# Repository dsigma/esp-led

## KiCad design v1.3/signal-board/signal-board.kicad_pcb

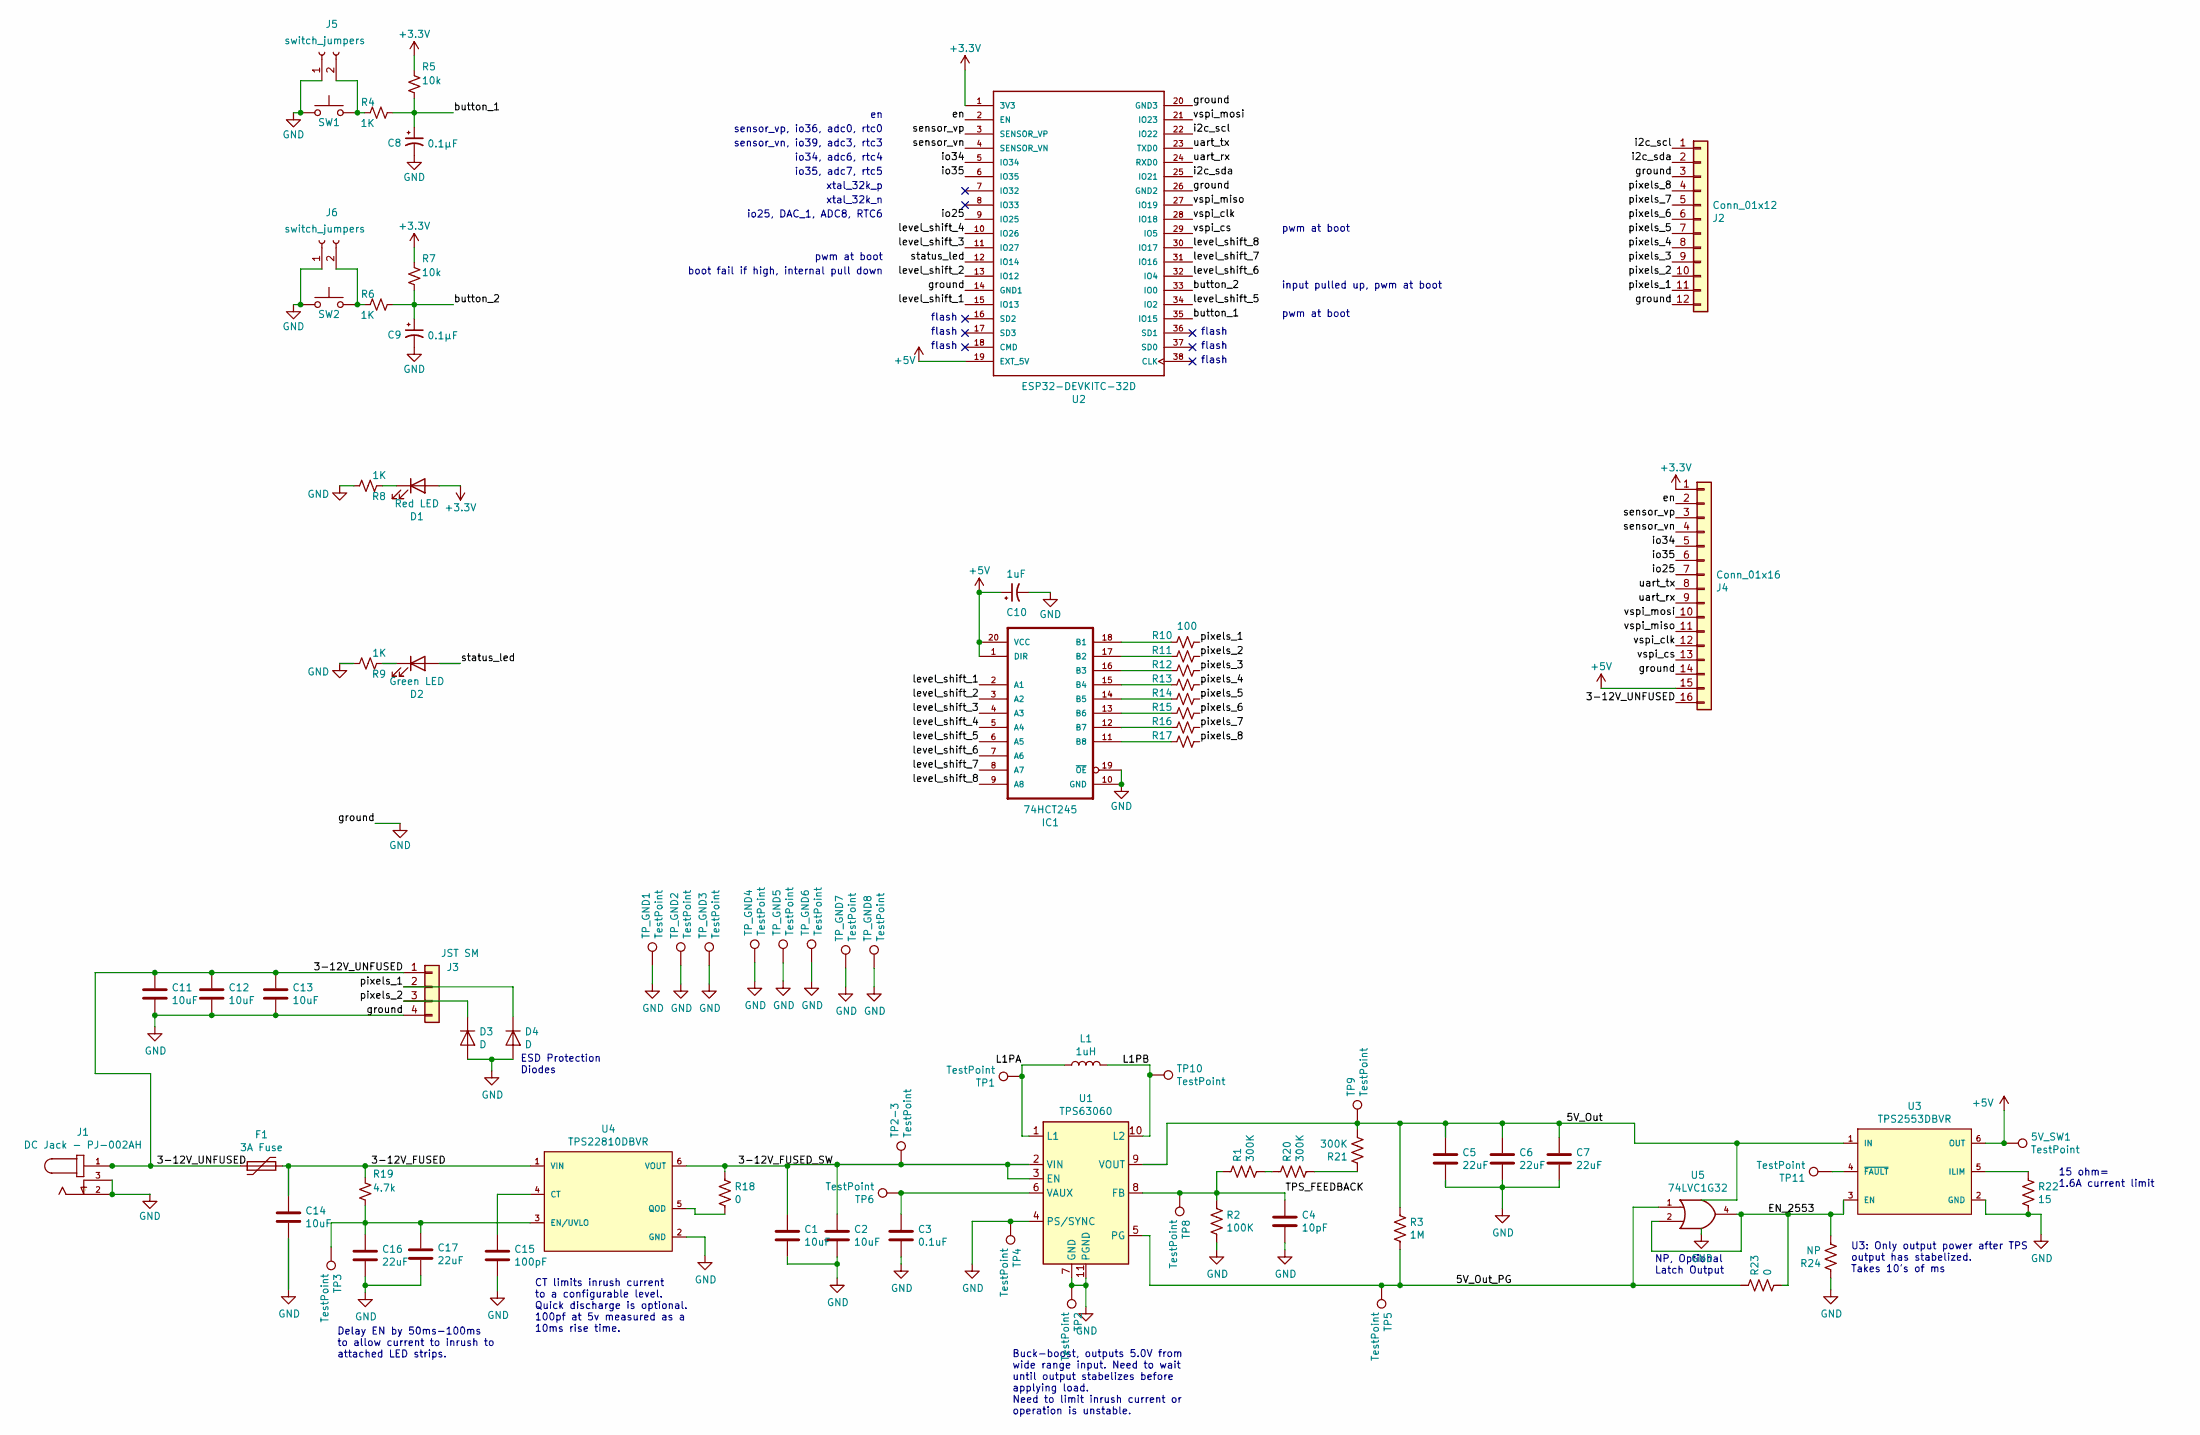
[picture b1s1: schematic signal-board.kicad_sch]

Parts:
5V_SW1: TestPoint; TestPoint_Pad_D1.0mm
C1, C2, C11, C12, C13, C14: 10uF; C_0805_2012Metric_Pad1.15x1.40mm_HandSolder; MouserPN 80-C0805C106K4PAC; DigiKeyPN 1276-6455-1-ND
C3: 0.1uF; C_0402_1005Metric; LCSC C1525
C4: 10pF; C_0402_1005Metric; LCSC C32949
C5, C6, C7: 22uF; C_0805_2012Metric_Pad1.15x1.40mm_HandSolder; MouserPN 81-GRM21BR61C226ME4L; DigiKeyPN 1276-6780-1-ND
C8, C9: 0.1µF; C_0402_1005Metric; LCSC C1525
C10: 1uF; C_0805_2012Metric_Pad1.15x1.40mm_HandSolder; LCSC C282736
C15: 100pF; C_0805_2012Metric_Pad1.15x1.40mm_HandSolder; LCSC C1790
C16, C17: 22uF; C_0805_2012Metric_Pad1.15x1.40mm_HandSolder; LCSC C45783
D1: Red LED; LED_0805_2012Metric; LCSC C84256
D2: Green LED; LED_0805_2012Metric; LCSC C2297
D3, D4: D; D_0603_1608Metric; LCSC C10677
F1: 3A Fuse; Fuse_1206_3216Metric; LCSC C182445
IC1: 74HCT245; SOIC-20W_7.5x10.0mm_P1.27mm; DigiKey100 0.336
J1: DC Jack - PJ-002AH; CUI_PJ-002AH
J2: Conn_01x12; PinHeader_1x12_P2.54mm_Vertical
J3: JST SM; jst-landing
J4: Conn_01x16; PinHeader_1x16_P2.54mm_Vertical
J5, J6: switch_jumpers; PinHeader_1x02_P2.54mm_Vertical
L1: 1uH; L_Taiyo-Yuden_NR-40xx_HandSoldering; MouserPN 963-NRS4018T1R0NDGJ; DigiKeyPN 587-2888-1-ND
R1, R20, R21: 300K; R_0402_1005Metric; LCSC C25774
R2: 100K; R_0402_1005Metric; LCSC C25741
R3: 1M; R_0402_1005Metric; LCSC C26083
R4, R6, R8, R9: 1K; R_0402_1005Metric; LCSC C11702
R5, R7: 10k; R_0402_1005Metric; LCSC C25744
R10, R11, R12, R13, R14, R15, R16, R17: 100; R_0805_2012Metric_Pad1.15x1.40mm_HandSolder; LCSC C17408
R18, R23: 0; R_0402_1005Metric; LCSC C17168
R19: 4.7k; R_0402_1005Metric; LCSC C25900
R22: 15; R_0402_1005Metric; LCSC C25083
R24: NP; R_0402_1005Metric
SW1, SW2: SW_MEC_5G; Tactile_Switch; LCSC C318886
TP1, TP2, TP2-3, TP3, TP4, TP5, TP6, TP8, TP9, TP10, TP11: TestPoint; TestPoint_Pad_D1.0mm
TP_GND1, TP_GND2, TP_GND3, TP_GND4, TP_GND5, TP_GND6, TP_GND7, TP_GND8: TestPoint; TestPoint_Pad_D1.0mm
U1: TPS63060; Texas_S-PWSON-N10_ThermalVias; MouserPN 595-TPS63060DSCR; DigiKey100 1.584
U2: ESP32-DEVKITC-32D; MODULE_ESP32-DEVKITC-32D
U3: TPS2553DBVR; SOT-23-6_Handsoldering; Rating Catalog; LCSC C55266
U4: TPS22810DBVR; SOT-23-6_Handsoldering; output voltage 18V; mouser part number 595-TPS22810DBVR; digikey description IC PWR SWITCH N-CHAN 1:1 6SOT23
U5: 74LVC1G32; SOT-353_SC-70-5_Handsoldering

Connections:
+3V3: D1.2 (A), J4.1, R5.1, R7.1, U2.1 (3V3)
+5V: 5V_SW1.1, C10.1, IC1.1 (DIR), IC1.20 (VCC), J4.15, U2.19 (EXT_5V), U3.6 (OUT)
/3-12V_FUSED: C14.1, F1.2, R19.1, U4.1 (VIN)
/3-12V_FUSED_SW: C1.1, C2.1, R18.1, TP2-3.1, U1.2 (VIN), U1.3 (EN), U4.6 (VOUT)
/3-12V_UNFUSED: C11.1, C12.1, C13.1, F1.1, J1.1, J3.1, J4.16
/5V_Out_PG: R3.2, R23.1, TP5.1, U1.5 (PG), U5.1
/EN_2553: R23.2, R24.2, U3.3 (EN), U5.2, U5.4
/L1PA: L1.1, TP1.1, U1.1 (L1)
/L1PB: L1.2, TP10.1, U1.10 (L2)
/TPS_FEEDBACK: C4.1, R1.1, R2.1, TP8.1, U1.8 (FB)
/button_1: C8.1, R4.2, R5.2, U2.35 (IO15)
/button_2: C9.1, R6.2, R7.2, U2.33 (IO0)
/en: J4.2, U2.2 (EN)
/i2c_scl: J2.1, U2.22 (IO22)
/i2c_sda: J2.2, U2.25 (IO21)
/io25: J4.7, U2.9 (IO25)
/io34: J4.5, U2.5 (IO34)
/io35: J4.6, U2.6 (IO35)
/level_shift_1: IC1.2 (A1), U2.15 (IO13)
/level_shift_2: IC1.3 (A2), U2.13 (IO12)
/level_shift_3: IC1.4 (A3), U2.11 (IO27)
/level_shift_4: IC1.5 (A4), U2.10 (IO26)
/level_shift_5: IC1.6 (A5), U2.34 (IO2)
/level_shift_6: IC1.7 (A6), U2.32 (IO4)
/level_shift_7: IC1.8 (A7), U2.31 (IO16)
/level_shift_8: IC1.9 (A8), U2.30 (IO17)
/pixels_1: D4.1 (K), J2.11, J3.2, R10.2
/pixels_2: D3.1 (K), J2.10, J3.3, R11.2
/pixels_3: J2.9, R12.2
/pixels_4: J2.8, R13.2
/pixels_5: J2.7, R14.2
/pixels_6: J2.6, R15.2
/pixels_7: J2.5, R16.2
/pixels_8: J2.4, R17.2
/sensor_vn: J4.4, U2.4 (SENSOR_VN)
/sensor_vp: J4.3, U2.3 (SENSOR_VP)
/status_led: D2.2 (A), U2.12 (IO14)
/uart_rx: J4.9, U2.24 (RXD0)
/uart_tx: J4.8, U2.23 (TXD0)
/vspi_clk: J4.12, U2.28 (IO18)
/vspi_cs: J4.13, U2.29 (IO5)
/vspi_miso: J4.11, U2.27 (IO19)
/vspi_mosi: J4.10, U2.21 (IO23)
GND: C1.2, C2.2, C3.2, C4.2, C5.2, C6.2, C7.2, C8.2, C9.2, C10.2, C11.2, C12.2, C13.2, C14.2, C15.2, C16.2, C17.2, D3.2 (A), D4.2 (A), IC1.10 (GND), IC1.19 (~OE~), J1.2, J1.3, J2.3, J2.12, J3.4, J4.14, J5.1, J6.1, R2.2, R8.2, R9.2, R22.2, R24.1, SW1.1 (A), SW1.2 (A), SW2.1 (A), SW2.2 (A), TP2.1, TP4.1, TP_GND1.1, TP_GND2.1, TP_GND3.1, TP_GND4.1, TP_GND5.1, TP_GND6.1, TP_GND7.1, TP_GND8.1, U1.4 (PS/SYNC), U1.7 (GND), U1.11 (PGND), U2.14 (GND1), U2.20 (GND3), U2.26 (GND2), U3.2 (GND), U4.2 (GND), U5.3 (GND)
unnamed: C3.1, TP6.1, U1.6 (VAUX)
unnamed: C15.1, U4.4 (CT)
unnamed: C16.1, C17.1, R19.2, TP3.1, U4.3 (EN/UVLO)
unnamed: D1.1 (K), R8.1
unnamed: D2.1 (K), R9.1
unnamed: IC1.11 (B8), R17.1
unnamed: IC1.12 (B7), R16.1
unnamed: IC1.13 (B6), R15.1
unnamed: IC1.14 (B5), R14.1
unnamed: IC1.15 (B4), R13.1
unnamed: IC1.16 (B3), R12.1
unnamed: IC1.17 (B2), R11.1
unnamed: IC1.18 (B1), R10.1
unnamed: J5.2, R4.1, SW1.3 (B), SW1.4 (B)
unnamed: J6.2, R6.1, SW2.3 (B), SW2.4 (B)
unnamed: R1.2, R20.1
unnamed: R18.2, U4.5 (QOD)
unnamed: R20.2, R21.1
unnamed: R22.1, U3.5 (ILIM)
unnamed: TP11.1, U3.4 (~FAULT~)
VCC: C5.1, C6.1, C7.1, R3.1, R21.2, TP9.1, U1.9 (VOUT), U3.1 (IN), U5.5 (VCC)

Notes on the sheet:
Delay EN by 50ms-100ms to allow current to inrush to attached LED strips.
ESD Protection Diodes
CT limits inrush current to a configurable level. Quick discharge is optional. 100pf at 5v measured as a 10ms rise time.
sensor_vp, io36, adc0, rtc0
sensor_vn, io39, adc3, rtc3
io34, adc6, rtc4
io35, adc7, rtc5
xtal_32k_p
xtal_32k_n
io25, DAC_1, ADC8, RTC6
pwm at boot
boot fail if high, internal pull down
flash
Buck-boost, outputs 5.0V from wide range input. Need to wait until output stabelizes before applying load. Need to limit inrush current or operation is unstable.
input pulled up, pwm at boot
NP, Optional Latch Output
U3: Only output power after TPS output has stabelized. Takes 10's of ms
15 ohm= 1.6A current limit

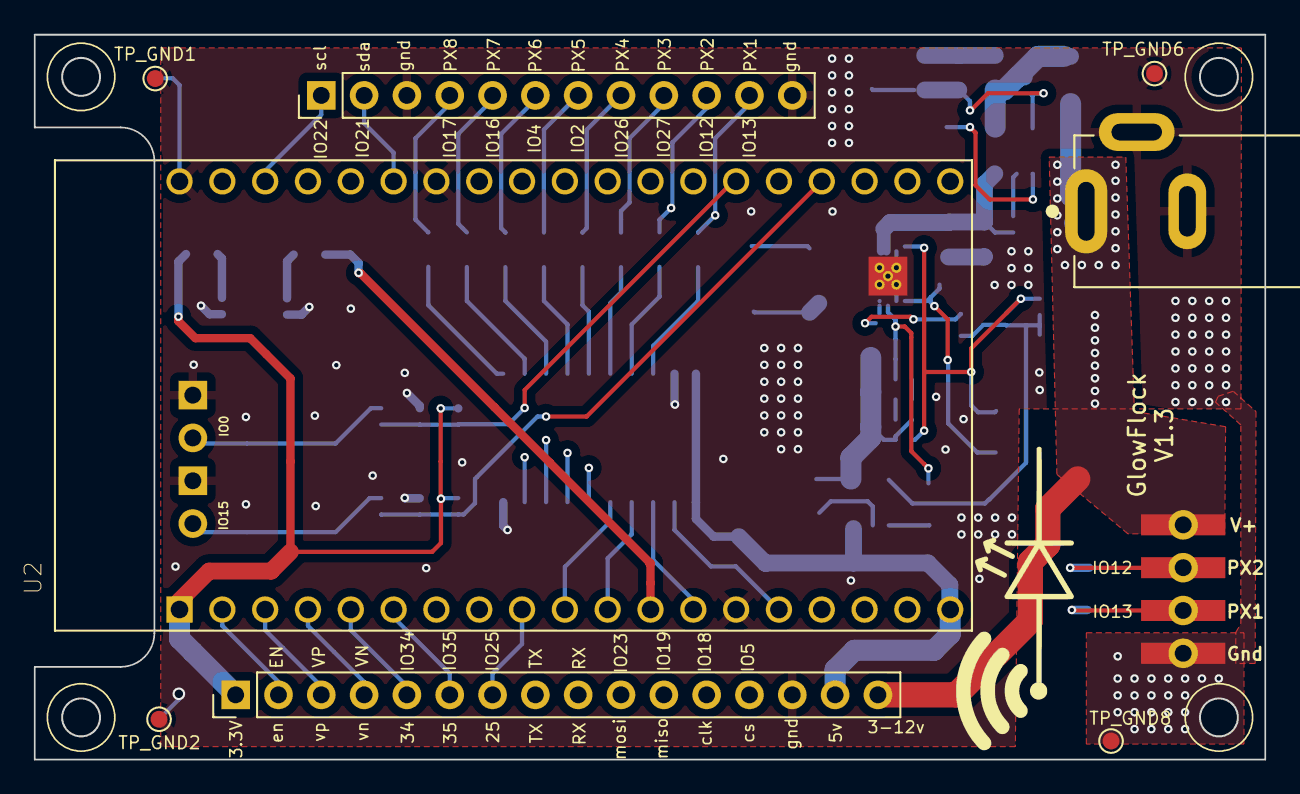
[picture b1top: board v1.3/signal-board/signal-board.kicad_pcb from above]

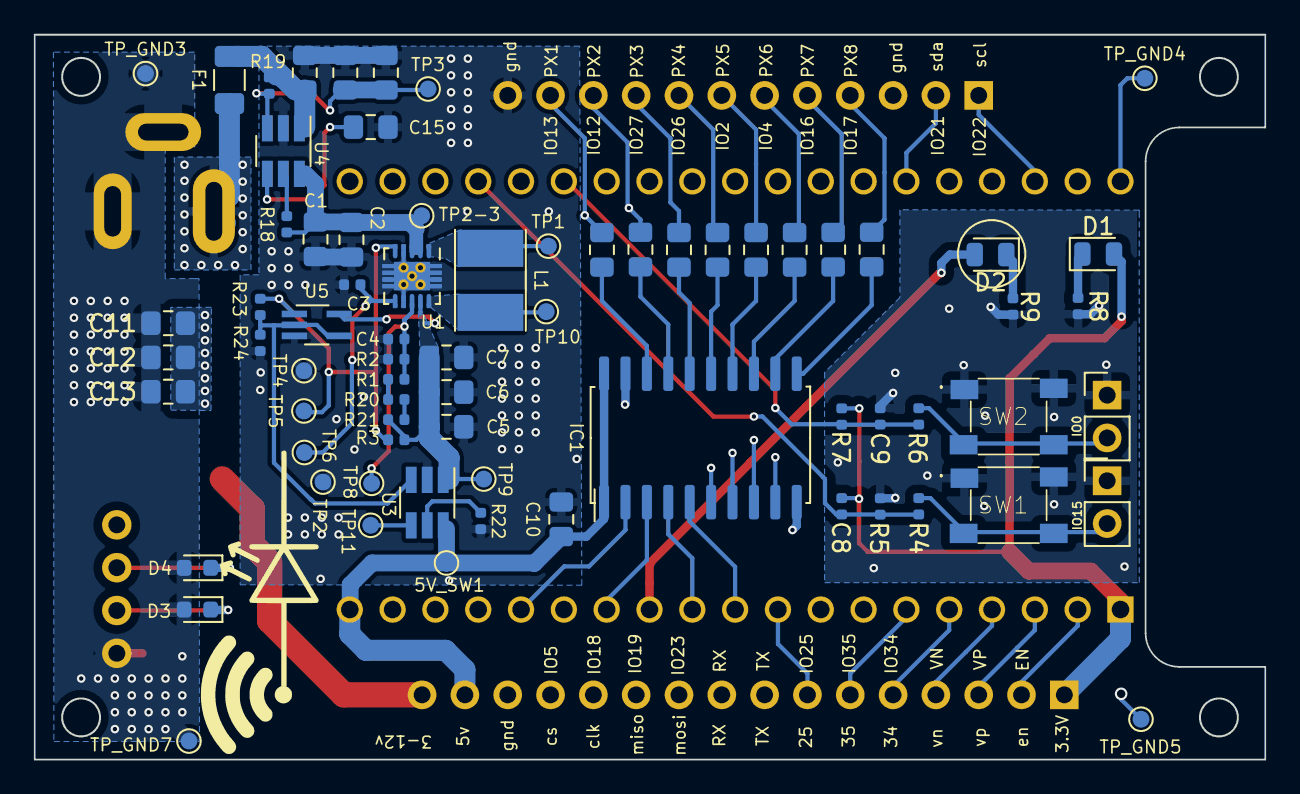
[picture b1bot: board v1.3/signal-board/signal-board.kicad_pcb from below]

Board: 4 copper layers, 73.0 x 43.0 mm, 81 parts (72 on the bottom side), 65 nets.

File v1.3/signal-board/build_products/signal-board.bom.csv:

Comment,Designator,Footprint,LCSC
"TestPoint","TP1,TP_GND1,TP2,TP_GND2,TP3,TP_GND3,TP4,TP_GND4,TP5,TP_GND5,TP6,TP_GND6,TP_GND7,TP8,TP_GND8,TP9,TP10,TP11,TP2-3,5V_SW1","TestPoint:TestPoint_Pad_D1.0mm",""
"10uF","C1,C2,C11,C12,C13,C14","Capacitor_SMD:C_0805_2012Metric_Pad1.15x1.40mm_HandSolder","C90545"
"1uF","C10","Capacitor_SMD:C_0805_2012Metric_Pad1.15x1.40mm_HandSolder","C282736"
"100pF","C15","Capacitor_SMD:C_0805_2012Metric_Pad1.15x1.40mm_HandSolder","C1790"
"0.1uF","C3","Capacitor_SMD:C_0402_1005Metric","C1525"
"10pF","C4","Capacitor_SMD:C_0402_1005Metric","C32949"
"22uF","C5,C6,C7,C16,C17","Capacitor_SMD:C_0805_2012Metric_Pad1.15x1.40mm_HandSolder","C45783"
"0.1µF","C8,C9","Capacitor_SMD:C_0402_1005Metric","C1525"
"Red LED","D1","LED_SMD:LED_0805_2012Metric","C84256"
"Green LED","D2","LED_SMD:LED_0805_2012Metric","C2297"
"D","D3,D4","Diode_SMD:D_0603_1608Metric","C10677"
"3A Fuse","F1","Fuse:Fuse_1206_3216Metric","C182445"
"74HCT245","IC1","GlowFlock footprints:SOIC-20W_7.5x10.0mm_P1.27mm","C133641"
"DC Jack - PJ-002AH","J1","GlowFlock footprints:CUI_PJ-002AH",""
"Conn_01x12","J2","Connector_PinHeader_2.54mm:PinHeader_1x12_P2.54mm_Vertical",""
"JST SM","J3","GlowFlock footprints:jst-landing",""
"Conn_01x16","J4","Connector_PinHeader_2.54mm:PinHeader_1x16_P2.54mm_Vertical",""
"switch_jumpers","J5,J6","Connector_PinHeader_2.54mm:PinHeader_1x02_P2.54mm_Vertical",""
"1uH","L1","Inductor_SMD:L_Taiyo-Yuden_NR-40xx_HandSoldering",""
"300K","R1,R20,R21","Resistor_SMD:R_0402_1005Metric","C25774"
"100","R10,R11,R12,R13,R14,R15,R16,R17","Resistor_SMD:R_0805_2012Metric_Pad1.15x1.40mm_HandSolder","C17408"
"0","R18,R23","Resistor_SMD:R_0402_1005Metric","C17168"
"4.7k","R19","Resistor_SMD:R_0402_1005Metric","C25900"
"100K","R2","Resistor_SMD:R_0402_1005Metric","C25741"
"15","R22","Resistor_SMD:R_0402_1005Metric","C25083"
"NP","R24","Resistor_SMD:R_0402_1005Metric",""
"1M","R3","Resistor_SMD:R_0402_1005Metric","C26083"
"1K","R4,R6,R8,R9","Resistor_SMD:R_0402_1005Metric","C11702"
"10k","R5,R7","Resistor_SMD:R_0402_1005Metric","C25744"
"SW_MEC_5G","SW1,SW2","GlowFlock footprints:Tactile_Switch","C318886"
"TPS63060","U1","Package_SON:Texas_S-PWSON-N10_ThermalVias",""
"ESP32-DEVKITC-32D","U2","GlowFlock footprints:MODULE_ESP32-DEVKITC-32D",""
"TPS2553DBVR","U3","Package_TO_SOT_SMD:SOT-23-6_Handsoldering","C55266"
"TPS22810DBVR","U4","Package_TO_SOT_SMD:SOT-23-6_Handsoldering","C205990"
"74LVC1G32","U5","Package_TO_SOT_SMD:SOT-353_SC-70-5_Handsoldering",""

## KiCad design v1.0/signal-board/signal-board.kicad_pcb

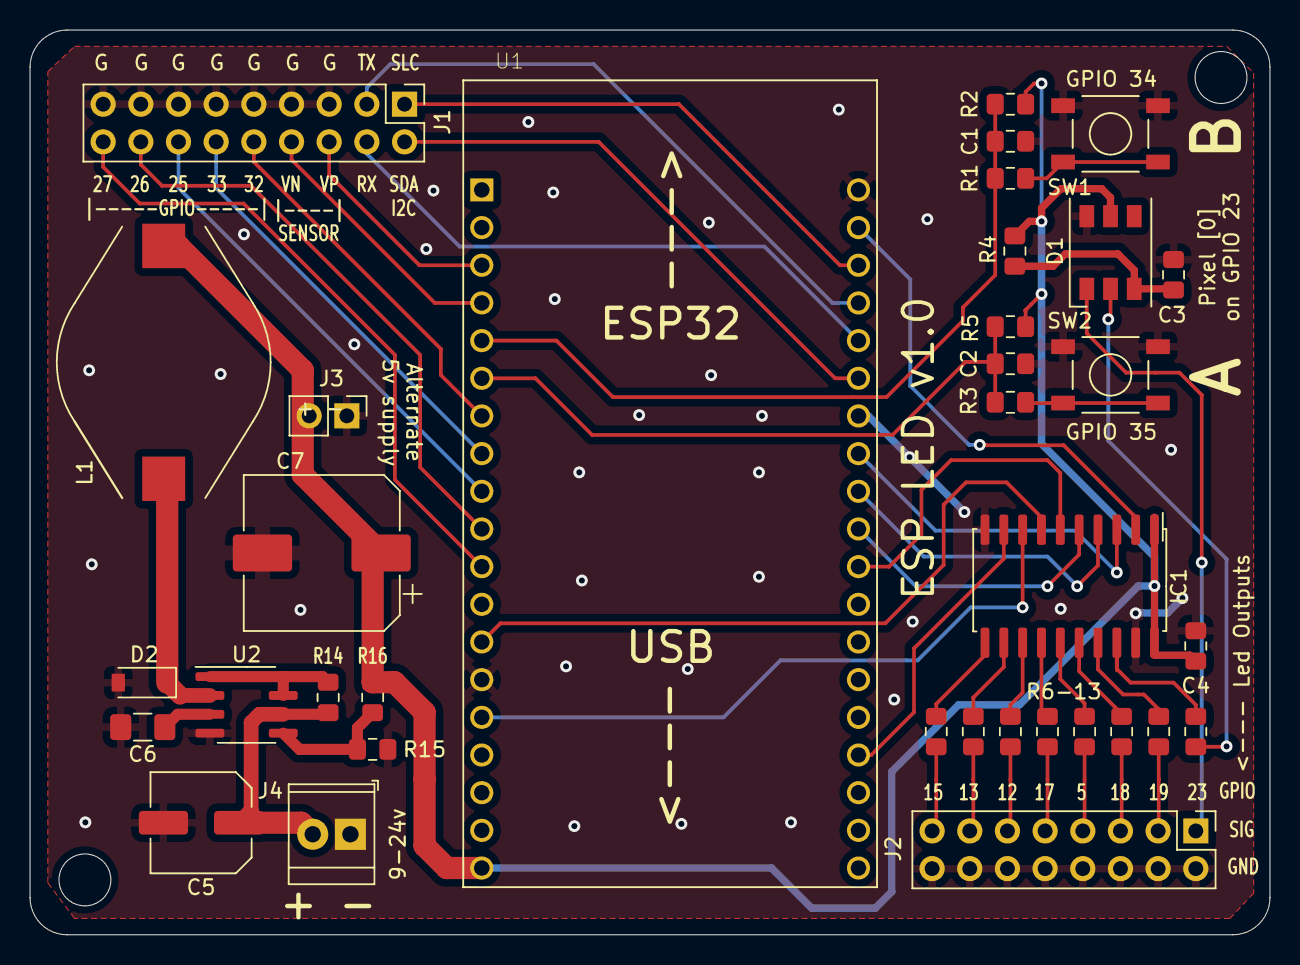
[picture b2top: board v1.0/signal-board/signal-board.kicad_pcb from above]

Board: 2 copper layers, 83.6 x 61.0 mm, 35 parts (0 on the bottom side), 48 nets.

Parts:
C1, C2, C3: 0.1µF; C_0805_2012Metric_Pad1.15x1.40mm_HandSolder
C4: 1uF; C_0805_2012Metric_Pad1.15x1.40mm_HandSolder
C5: 100uF; C_Elec_6.3x7.7
C6: 470pF; C_1206_3216Metric_Pad1.42x1.75mm_HandSolder
C7: 220uF; CP_Elec_10x10
D1: WS2812; LED_WS2812_PLCC6_5.0x5.0mm_P1.6mm
D2: 1N5819; D_SOD-123
IC1: 74HCT245; SOIC-20W_7.5x10.0mm_P1.27mm
J1: Conn_02x09_Odd_Even; PinHeader_2x09_P2.54mm_Vertical
J2: Conn_02x08_Odd_Even; PinHeader_2x08_P2.54mm_Vertical
J3: 5V Pwr Conn; PinHeader_1x02_P2.54mm_Vertical
J4: 24V Screw Term; TerminalBlock_TE_282834-2_1x02_P2.54mm_Horizontal
L1: 220uH; L_Bourns_SDR1806
R1, R3: 1k; R_0805_2012Metric_Pad1.15x1.40mm_HandSolder
R2, R5: 10k; R_0805_2012Metric_Pad1.15x1.40mm_HandSolder
R4: 150; R_0805_2012Metric_Pad1.15x1.40mm_HandSolder
R6, R7, R8, R9, R10, R11, R12, R13: 100; R_0805_2012Metric_Pad1.15x1.40mm_HandSolder
R14: 0.33 ohms; R_0805_2012Metric_Pad1.15x1.40mm_HandSolder
R15: 1.2K; R_0805_2012Metric_Pad1.15x1.40mm_HandSolder
R16: 3.6K; R_0805_2012Metric_Pad1.15x1.40mm_HandSolder
SW1, SW2: SW_MEC_5G; SW_PTS525SM15SMTR2LFS
U1: ESP32-DEVKITC-32D; MODULE_ESP32-DEVKITC-32D
U2: MC33063AD; SOIC-8_3.9x4.9mm_P1.27mm

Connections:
7V_to_24V_Input: C5.1, J4.2, R14.1, U2.6
+5V: C4.1, C7.1, D1.5, IC1.1, IC1.20, J3.2, L1.2, R2.1, R4.1, R5.1, R16.2, U1.19
GND: C1.2, C2.2, C3.2, C4.2, C5.2, C6.2, C7.2, D1.6, D2.2, IC1.10, IC1.19, J1.5, J1.7, J1.9, J1.11, J1.13, J1.15, J1.17, J2.2, J2.4, J2.6, J2.8, J2.10, J2.12, J2.14, J2.16, J3.1, J4.1, R15.2, SW1.1, SW1.2, SW2.1, SW2.2, U1.14, U1.20, U1.26, U2.4
unnamed: C1.1, R1.2, R2.2, U1.5
unnamed: C2.1, R3.2, R5.2, U1.6
unnamed: C3.1, D1.3, R4.2
unnamed: C6.1, U2.3
unnamed: D1.1, J2.1
unnamed: D1.2, R6.2
unnamed: D2.1, L1.1, U2.2
unnamed: IC1.2, U1.21
unnamed: IC1.3, U1.27
unnamed: IC1.4, U1.28
unnamed: IC1.5, U1.29
unnamed: IC1.6, U1.30
unnamed: IC1.7, U1.13
unnamed: IC1.8, U1.15
unnamed: IC1.9, U1.35
unnamed: IC1.11, R13.1
unnamed: IC1.12, R12.1
unnamed: IC1.13, R11.1
unnamed: IC1.14, R10.1
unnamed: IC1.15, R9.1
unnamed: IC1.16, R8.1
unnamed: IC1.17, R7.1
unnamed: IC1.18, R6.1
unnamed: J1.1, U1.22
unnamed: J1.2, U1.25
unnamed: J1.3, U1.23
unnamed: J1.4, U1.24
unnamed: J1.6, U1.3
unnamed: J1.8, U1.4
unnamed: J1.10, U1.7
unnamed: J1.12, U1.8
unnamed: J1.14, U1.9
unnamed: J1.16, U1.10
unnamed: J1.18, U1.11
unnamed: J2.3, R7.2
unnamed: J2.5, R8.2
unnamed: J2.7, R9.2
unnamed: J2.9, R10.2
unnamed: J2.11, R11.2
unnamed: J2.13, R12.2
unnamed: J2.15, R13.2
unnamed: R1.1, SW1.3, SW1.4
unnamed: R3.1, SW2.3, SW2.4
unnamed: R14.2, U2.1, U2.7, U2.8
unnamed: R15.1, R16.1, U2.5

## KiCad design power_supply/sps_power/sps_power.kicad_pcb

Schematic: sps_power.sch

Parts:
C1: 100uF; CP_Radial_D5.0mm_P2.50mm
C2: 470pF; C_1206_3216Metric_Pad1.42x1.75mm_HandSolder
C3: 220uF; CP_Elec_10x10
D1: 1N5819; D_SOD-123
J1: 5V Pwr Conn; PinHeader_1x02_P1.00mm_Vertical
L1: 220uH; L_Bourns-SRR1005
R1: 0.33 ohms; R_0805_2012Metric_Pad1.15x1.40mm_HandSolder
R2: 1.2K; R_0805_2012Metric_Pad1.15x1.40mm_HandSolder
R3: 3.8K; R_0805_2012Metric_Pad1.15x1.40mm_HandSolder
U1: MC33063AD; SOIC-8_3.9x4.9mm_P1.27mm

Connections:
+24V: C1.1, R1.1, U1.6 (Vin)
GND: C1.2, C2.2, C3.2, D1.2 (A), J1.1, R2.2, U1.4 (GND)
unnamed: C2.1, U1.3 (TC)
unnamed 3: C3.1, J1.2, L1.2, R3.2; also elsewhere on the board
unnamed: D1.1 (K), L1.1, U1.2 (SwE)
unnamed: R1.2, U1.1 (SwC), U1.7 (Ipk), U1.8 (DC)
unnamed: R2.1, R3.1, U1.5 (Vfb)

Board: 2 copper layers, 11 parts (0 on the bottom side), 7 nets, no tracks yet.

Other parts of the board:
TP1: 5V_Out; TestPoint_Pad_D2.0mm

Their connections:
unnamed 3: TP1.1; also elsewhere on the board

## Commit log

2020-03-28 datasheet and footprints
2020-03-29 basic signal flow schematic
2020-03-29 Rough layout for power supply circuit
2020-03-29 Interum commit
2020-03-30 Interum power supply cad commit
2020-03-30 ignore stuff
2020-03-30 more signal board
2020-03-31 BOM made
2020-03-31 some footprints
2020-04-02 signal board stufffffff
2020-04-02 Copied power supply circuit into signal board schematic, initial creation of PCB
2020-04-03 More footprints and rough layout of pcb
2020-04-06 traces 1.0 done
2020-04-07 Updated packages footprints and added ground plane stitching
2020-04-07 A B, esp direction, holes
2020-04-10 Updated resistor part numbers on feedback circuit for power supply
2020-04-16 art and design rules
2020-04-16 correcting warnings
2020-04-17 Fixed DRC check error with alternate 5V supply footprint using 2.54mm instead of 1.0mm 1x2 header
2020-05-02 Added blinky light sample code for the ESP-LED PCB
2020-05-02 added datasheet
2020-08-18 v2 progress on schematic
2020-08-18 schematic re-org
2020-08-26 footprint updates
2020-08-27 layout
2020-08-27 JLC PCB changes
2020-09-19 updated v1.1 power layout
2020-09-20 updated notes and updates from board review
2020-10-13 circuit updates
2020-10-13 oops
2020-10-13 build files for JLCPCB
2020-10-13 kicad BOM generator util for JLCPCB
2020-11-22 added v1.2 folder
2020-11-22 gitignore backups
2020-11-22 added holes to corners
2020-11-22 reorganized footprints and symbols
2020-11-22 removed backups
2020-11-22 garbage in gitignore
2020-11-22 updated symbol and footprint links
2020-11-22 got rid of footprints, added new dc jack
2020-11-23 cleanup, new plug
2020-12-28 updates for v1.2
2021-03-12 1.3 board
